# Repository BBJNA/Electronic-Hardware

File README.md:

# Electromechanical Engineering Project for Wentworth Institute of Technology (2018)

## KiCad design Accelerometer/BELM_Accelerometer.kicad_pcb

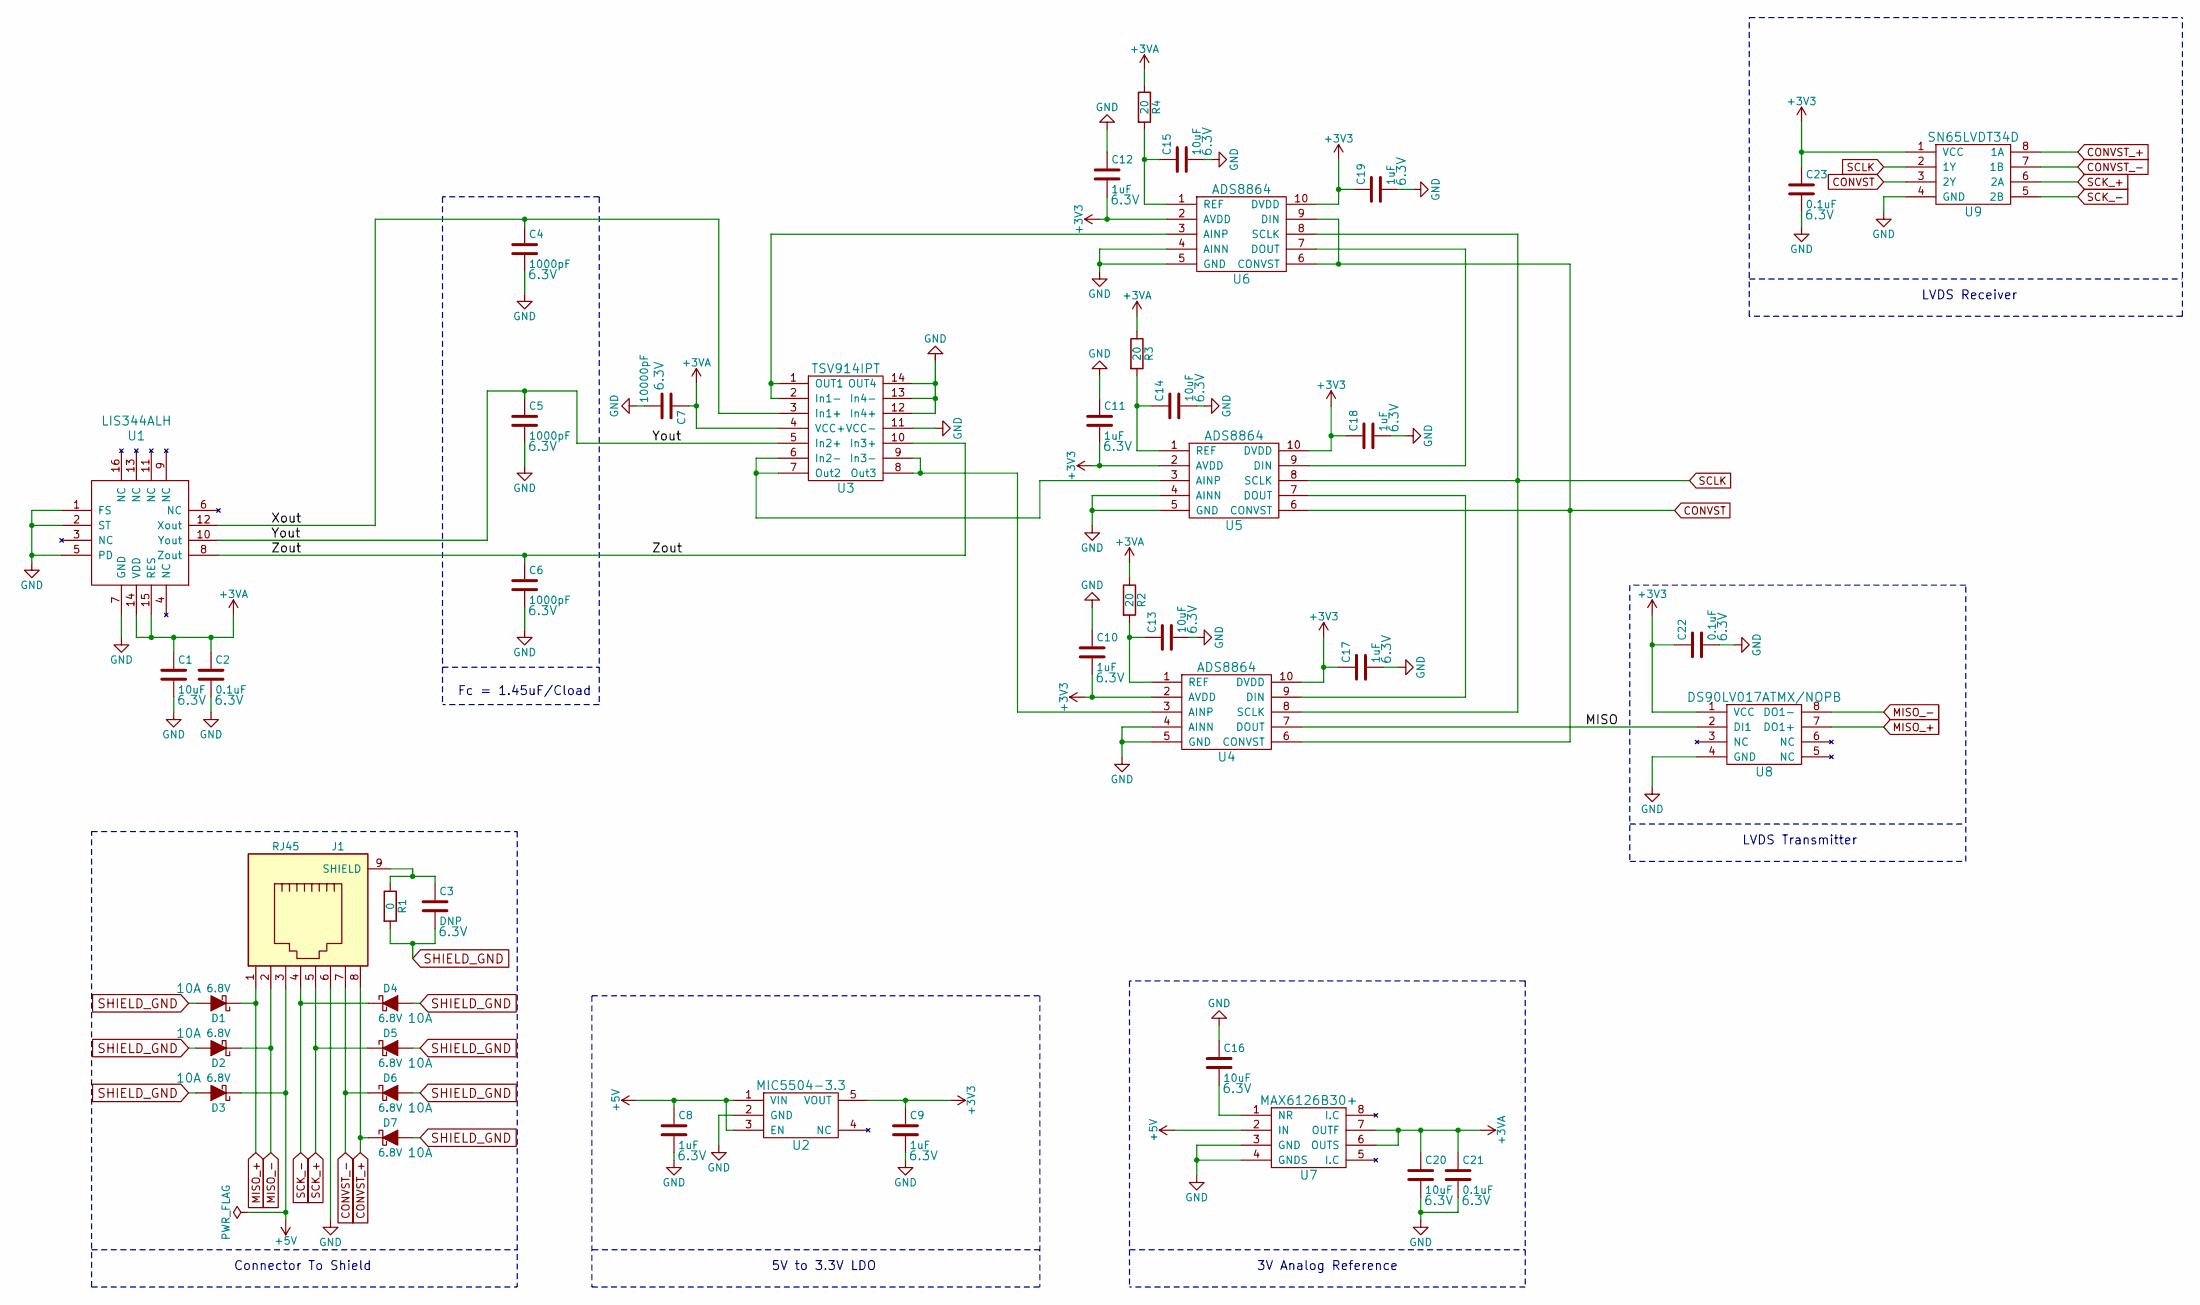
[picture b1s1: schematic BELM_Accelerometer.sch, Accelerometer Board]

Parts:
C1, C13, C14, C15, C16, C20: 10uF; C_0603; Voltage 6.3V
C2, C21, C22, C23: 0.1uF; C_0402; Voltage 6.3V
C3: DNP; C_0805; Voltage 6.3V
C4, C5, C6: 1000pF; C_0402; Voltage 6.3V
C7: 10000pF; C_0402; Voltage 6.3V
C8, C9, C10, C11, C12, C17, C18, C19: 1uF; C_0603; Voltage 6.3V
D1, D2, D3, D4, D5, D6, D7: 6.8V; SOD-123FL
J1: RJ45; A-2004-2-4-LPS-N-R
R1: 0; R_0805
R2, R3, R4: 20; R_0603
U1: LIS344ALH; 16-LGA
U2: MIC5504-3.3; SOT-23-5
U3: TSV914IPT; TSSOP-14_4.4x5mm_Pitch0.65mm
U4, U5, U6: ADS8864; TSSOP-10_3x3mm_Pitch0.5mm
U7: MAX6126B30+; uMAX
U8: DS90LV017ATMX/NOPB; SOIC-8_3.9x4.9mm_Pitch1.27mm
U9: SN65LVDT34D; SOIC-8_3.9x4.9mm_Pitch1.27mm

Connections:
+3V3: C9.1, C10.2, C11.2, C12.2, C17.1, C18.1, C19.1, C22.1, C23.1, U2.5 (VOUT), U4.2 (AVDD), U4.10 (DVDD), U5.2 (AVDD), U5.10 (DVDD), U6.2 (AVDD), U6.10 (DVDD), U8.1 (VCC), U9.1 (VCC)
+3VA: C1.1, C2.1, C7.1, C20.1, C21.1, R2.1, R3.1, R4.1, U1.14 (VDD), U1.15 (RES), U3.4 (VCC+), U7.6 (OUTS), U7.7 (OUTF)
+5V: C8.1, D3.1 (K), J1.3, U2.1 (VIN), U2.3 (EN), U7.2 (IN)
/MISO: U4.7 (DOUT), U8.2 (DI1)
/Xout: C4.1, U1.12 (Xout), U3.3 (In1+)
/Yout: C5.1, U1.10 (Yout), U3.5 (In2+)
/Zout: C6.1, U1.8 (Zout), U3.10 (In3+)
CONVST: U4.6 (CONVST), U5.6 (CONVST), U6.6 (CONVST), U6.9 (DIN), U9.3 (2Y)
CONVST_+: D7.1 (K), J1.8, U9.8 (1A)
CONVST_-: D6.1 (K), J1.7, U9.7 (1B)
GND: C1.2, C2.2, C4.2, C5.2, C6.2, C7.2, C8.2, C9.2, C10.1, C11.1, C12.1, C13.2, C14.2, C15.2, C16.1, C17.2, C18.2, C19.2, C20.2, C21.2, C22.2, C23.2, J1.6, U1.1 (FS), U1.2 (ST), U1.5 (PD), U1.7 (GND), U2.2 (GND), U3.11 (VCC-), U3.12 (In4+), U3.13 (In4-), U3.14 (OUT4), U4.4 (AINN), U4.5 (GND), U5.4 (AINN), U5.5 (GND), U6.4 (AINN), U6.5 (GND), U7.3 (GND), U7.4 (GNDS), U8.4 (GND), U9.4 (GND)
MISO_+: D1.1 (K), J1.1, U8.7 (DO1+)
MISO_-: D2.1 (K), J1.2, U8.8 (DO1-)
unnamed: C3.1, J1.9 (SHIELD), R1.1
unnamed: C13.1, R2.2, U4.1 (REF)
unnamed: C14.1, R3.2, U5.1 (REF)
unnamed: C15.1, R4.2, U6.1 (REF)
unnamed: C16.2, U7.1 (NR)
unnamed: U3.1 (OUT1), U3.2 (In1-), U6.3 (AINP)
unnamed: U3.6 (In2-), U3.7 (Out2), U5.3 (AINP)
unnamed: U3.8 (Out3), U3.9 (In3-), U4.3 (AINP)
unnamed: U4.9 (DIN), U5.7 (DOUT)
unnamed: U5.9 (DIN), U6.7 (DOUT)
SCK_+: D5.1 (K), J1.5, U9.6 (2A)
SCK_-: D4.1 (K), J1.4, U9.5 (2B)
SCLK: U4.8 (SCLK), U5.8 (SCLK), U6.8 (SCLK), U9.2 (1Y)
SHIELD_GND: C3.2, D1.2 (A), D2.2 (A), D3.2 (A), D4.2 (A), D5.2 (A), D6.2 (A), D7.2 (A), R1.2

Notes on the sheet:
Fc = 1.45uF/Cload
3V Analog Reference
Connector To Shield
5V to 3.3V LDO
LVDS Receiver
LVDS Transmitter

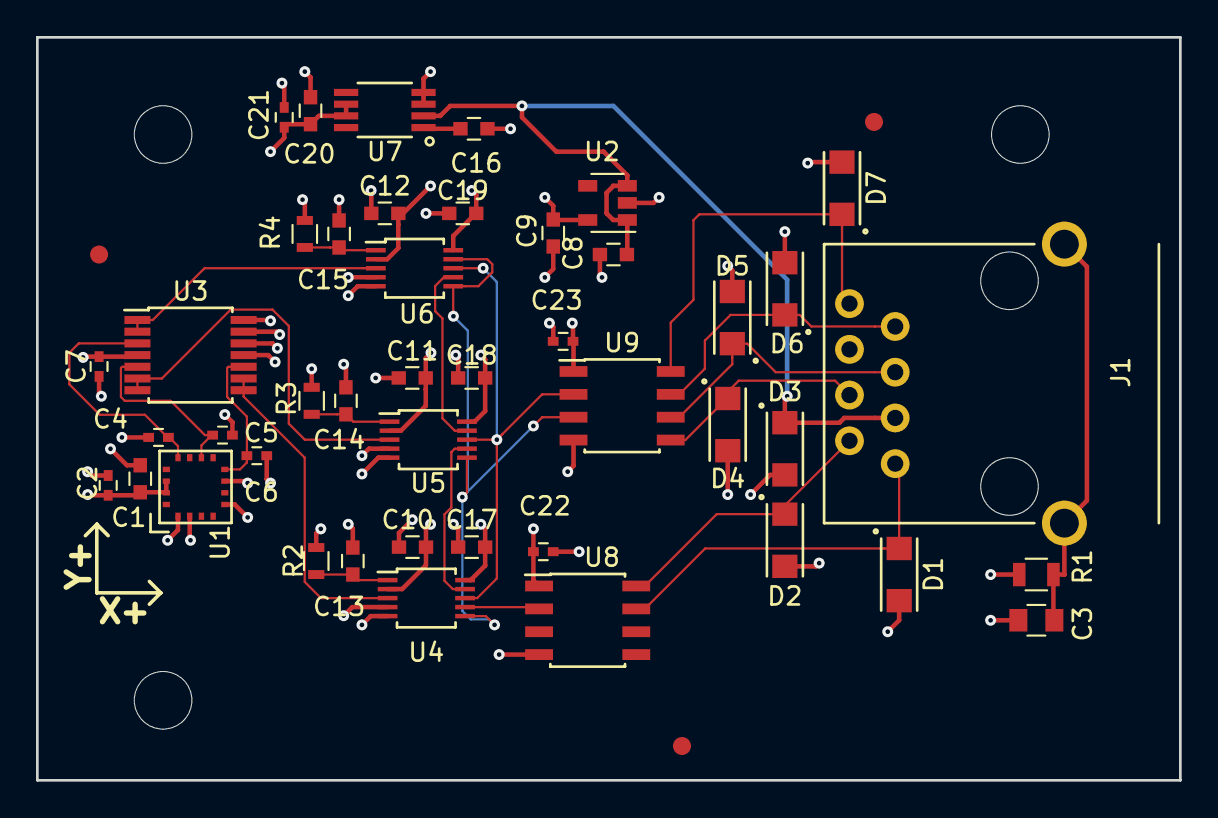
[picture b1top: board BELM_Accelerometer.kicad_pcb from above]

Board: 4 copper layers, 63.5 x 41.3 mm, 44 parts (0 on the bottom side), 27 nets.

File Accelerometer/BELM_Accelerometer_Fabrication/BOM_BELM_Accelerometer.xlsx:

Title: | S.I.R. Accelerometer Boards
Date: | 43070
Contact | jwilliams@shelltechworks.com
Total Number of Parts: | 296
Number of Boards: | 8
Number of Parts per Board: | 43
Number of Unique Parts per Board: | 17
Total Estimated Cost for Parts: | 310.73279999999994
REF | Part | Digikey Part | Value | Price/Qty | Qty/Board | Total Qty | Total Price | Link | Desicription of part
C1 C13 C14 C15 C16 C20 | GRM188R60J106KE47D | 490-12538-1-ND | 10uF | 0.109 | 6 | 48 | 5.2320000000000002 | https://www.digikey.com/product-detail/en/murata-electronics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 | CAP CER 10UF 6.3V X5R 0603
C2 C21 C22 C23 | C0402C104K9RACTU | 399-4872-1-ND | 0.1uf | 6.3E-2 | 4 | 32 | 2.016 | https://www.digikey.com/product-detail/en/kemet/C0402C104K9R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 | CAP CER 0.1UF 6.3V X7R 0402
C4 C5 C6 | C0402C102K9RACTU | 399-8941-1-ND | 1000pF | 1.9E-2 | 3 | 24 | 0.45599999999999996 | https://www.digikey.com/product-detail/en/kemet/C0402C102K9R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 | CAP CER 1000PF 6.3V X7R 0402
C7 | GRM155R70J103KA01D | 490-6318-1-ND | 10000pF | 2.5999999999999999E-2 | 1 | 8 | 0.20799999999999999 | https://www.digikey.com/product-detail/en/murata-electronics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 | CAP CER 10000PF 6.3V X7R 0402
C8 C9 C10 C11 C12 C17 C18 C19 | CL10B105KQ8NNNC | 1276-1024-1-ND | 1uF | 4.1000000000000002E-2 | 8 | 64 | 2.6240000000000001 | https://www.digikey.com/product-detail/en/samsung-electro-me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 | CAP CER 1UF 6.3V X7R 0603
D1 D2 D3 D4 D5 D6 D7 | SMF3.3 | F7701CT-ND | 6.8V 10A | 0.39079999999999998 | 7 | 56 | 21.884799999999998 | https://www.digikey.com/product-detail/en/littelfuse-inc/SMF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 | TVS DIODE 3.3VWM 6.8VC SOD123F
J1 | A-2004-2-4-LPS-N-R | AE10387-ND | RJ45 CONN | 0.93200000000000005 | 1 | 8 | 7.4560000000000004 | https://www.digikey.com/product-detail/en/assmann-wsw-compon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 | CONN MOD JACK 8P8C R/A SHIELDED
R1 | RC0805JR-070RL | 311-0.0ARCT-ND | 0 OHM | 0.1 | 1 | 8 | 0.8 | https://www.digikey.com/product-detail/en/yageo/RC0805JR-070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 | RES SMD 0 OHM JUMPER 1/8W 0805
R2 R3 R4 | RNCP0603FTD20R0 | RNCP0603FTD20R0CT-ND | 20 OHM | 0.03 | 3 | 24 | 0.72 | https://www.digikey.com/product-detail/en/stackpole-electron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 | RES SMD 20 OHM 1% 1/8W 0603
U1 | LIS344ALHTR | 497-6345-1-ND |  | 3.9929999999999999 | 1 | 8 | 31.943999999999999 | https://www.digikey.com/product-detail/en/stmicroelectronics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 | ACCELEROMETER 2-6G ANALOG 16LGA
U2 | MIC5504-3.3YM5-TR | 576-4764-1-ND | 3.3V | 0.12 | 1 | 8 | 0.96 | https://www.digikey.com/product-detail/en/microchip-technolo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 | IC REG LINEAR 3.3V 300MA SOT23-5
U3 | TSV914IPT | 497-5832-1-ND |  | 1.1499999999999999 | 1 | 8 | 9.1999999999999993 | https://www.digikey.com/product-detail/en/stmicroelectronics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 | IC OPAMP GP 8MHZ RRO 14TSSOP
U4 U5 U6 | ADS8864IDGSR | 296-39881-1-ND |  | 7.6980000000000004 | 3 | 24 | 184.75200000000001 | https://www.digikey.com/product-detail/en/texas-instruments/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 | IC ADC 16BIT 680KSPS 10VSSOP
U7 | MAX6126B30+ | MAX6126B30+-ND | 3V | 3.83 | 1 | 8 | 30.64 | https://www.digikey.com/product-detail/en/maxim-integrated/M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 | IC VREF SERIES 3V 8UMAX
U8 | DS90LV017ATMX/NOPB | 296-35387-1-ND |  | 1.48 | 1 | 8 | 11.84 | https://www.digikey.com/product-detail/en/texas-instruments/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 | IC DRIVER SINGLE HS DIFF 8-SOIC
U9 | SN65LVDT34D | 296-9751-5-ND |  | 2.8 | 1 | 8 | 22.4 | https://www.digikey.com/product-detail/en/texas-instruments/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 | IC DIFF RECEIVER DUAL HS 8-SOIC
C3 | DNP | DNP | DNP | 0 | 0 | 0 | DNP | DNP | DNP

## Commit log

2017-11-08 Accelerometer placed with initial connections
2017-11-19 First Rev to Review
2017-11-19 REV1
2017-11-19 Rev 1
2017-11-19 With PDF
2017-11-21 Update PCB
2017-11-27 Update 11272017
2017-11-28 For Todd Tomorrow
2017-11-29 Todd's Revisions
2017-11-30 Final Review
2017-11-30 Final
2017-11-30 Fiducials
2017-12-01 Lee Edits
2017-12-01 Lee Updates
2017-12-01 UPdatig
2017-12-07 Finalized
2018-01-24 RPi Inital Commit
2018-01-30 Hello
